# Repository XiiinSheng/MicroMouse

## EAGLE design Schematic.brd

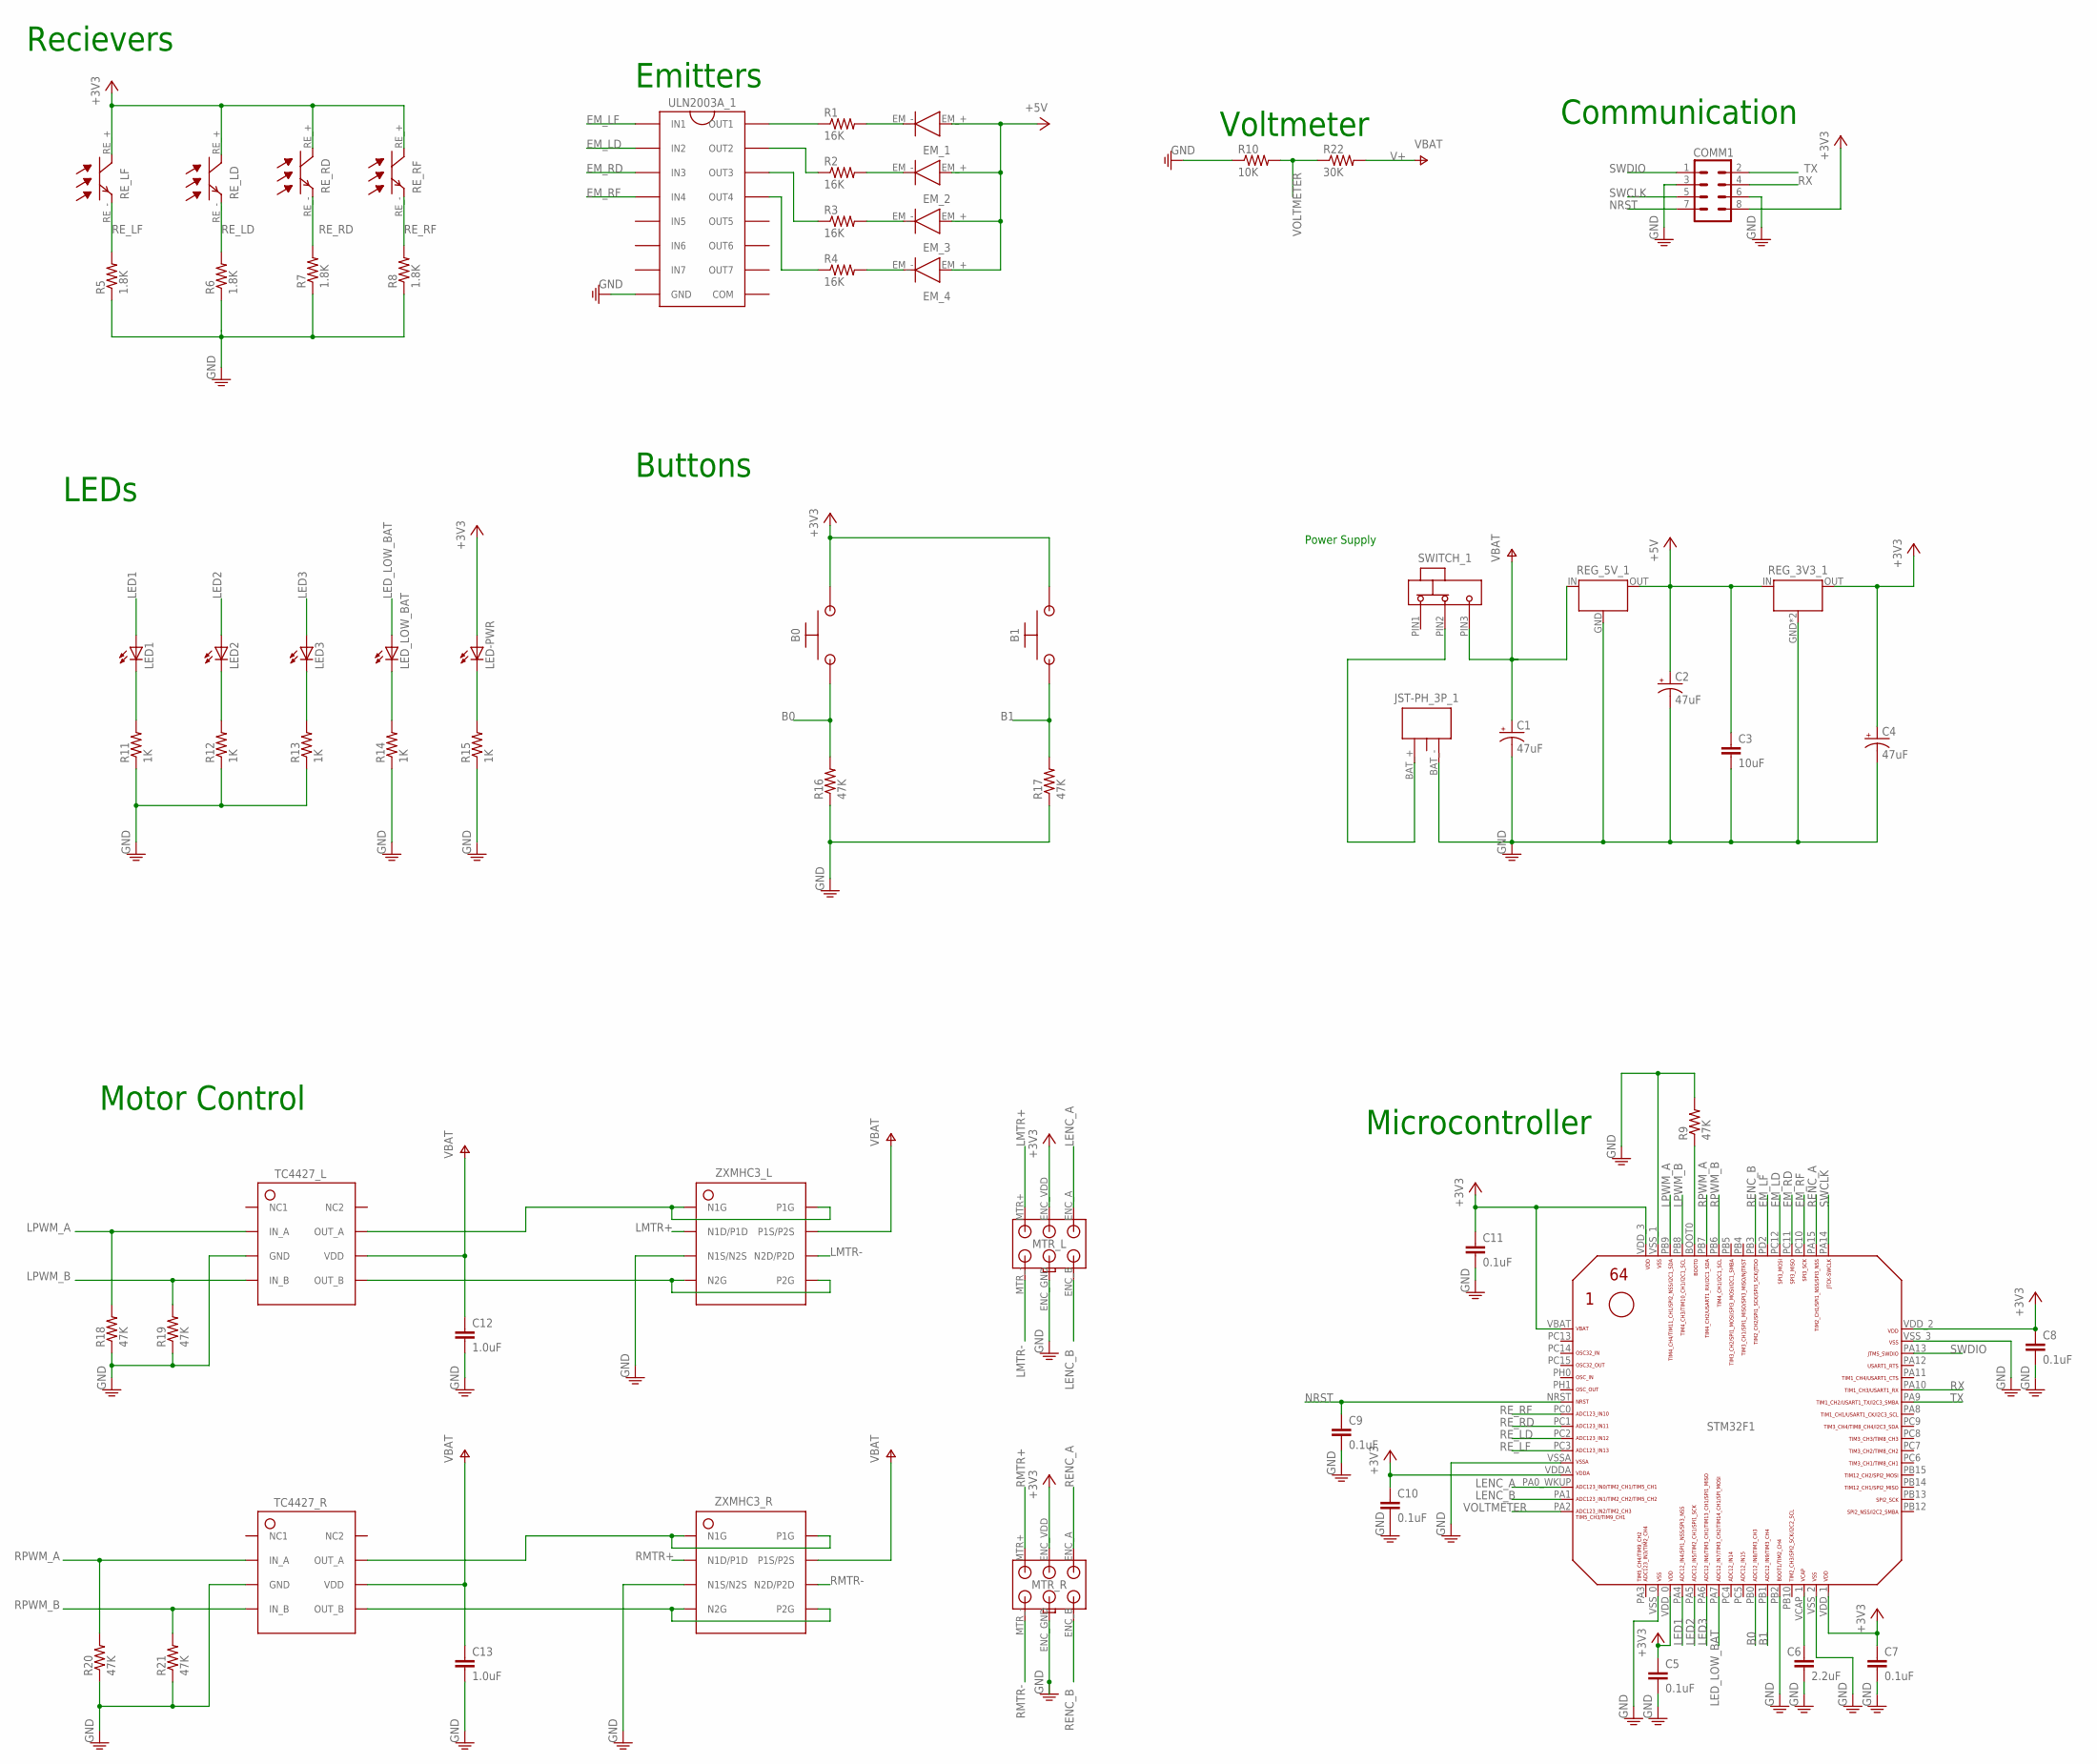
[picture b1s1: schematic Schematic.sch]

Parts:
B0, B1: POLOLU_BUTTON
C1, C2, C4: 47uF; CAP_TANT_1210IN_3528MM
C3: 10uF; 0805
C5, C7, C8, C9, C10, C11: 0.1uF; 0805
C6: 2.2uF; 0805
C12, C13: 1.0uF; 0805
COMM1: M04X2; 2X4
EM_1, EM_2, EM_3, EM_4: SFH4545; EMITTER
JST-PH_3P_1: 3PIN; B3B-PH-K-S
LED1, LED2, LED3: LED; LED-0805
LED-PWR: LED; LED-0805
LED_LOW_BAT: LED; LED-0805
MTR_L: MOTOR_ENCODER_HEADER
MTR_R: MOTOR_ENCODER_HEADER
R1, R2, R3, R4: 16K; 0805
R5, R6, R7, R8: 1.8K; 0805
R9, R16, R17, R18, R19, R20, R21: 47K; 0805
R10: 10K; 0805
R11, R12, R13, R14, R15: 1K; 0805
R22: 30K; 0805
REG_3V3_1: 3V3_REG; SOT223
REG_5V_1: REG_5V_MURATA; 5V_REG_MURATA
RE_LD: TEFT4300; RECEIVER
RE_LF: TEFT4300; RECEIVER
RE_RD: TEFT4300; RECEIVER
RE_RF: TEFT4300; RECEIVER
STM32F1: STM32F4_401_410_411_412_413_446; LQFP64
SWITCH_1: POLOLU_SWITCH
TC4427_L, TC4427_R: TC4427_SOIC8
ULN2003A_1: ULN2003A
ZXMHC3_L, ZXMHC3_R: ZXMHC3

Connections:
+3V3: B0.P$2 (2), B1.P$2 (2), C4.A (+), C5.1, C7.1, C8.1, C10.1, C11.1, COMM1.8, LED-PWR.A, MTR_L.ENC_VDD, MTR_R.ENC_VDD, REG_3V3_1.OUT, RE_LD.RE_+ (C), RE_LF.RE_+ (C), RE_RD.RE_+ (C), RE_RF.RE_+ (C), STM32F1.VBAT, STM32F1.VDDA, STM32F1.VDD_0, STM32F1.VDD_1, STM32F1.VDD_2, STM32F1.VDD_3
+5V: C2.A (+), C3.1, EM_1.EM_+ (+), EM_2.EM_+ (+), EM_3.EM_+ (+), EM_4.EM_+ (+), REG_3V3_1.IN, REG_5V_1.OUT
B0: B0.P$1 (1), R16.2, STM32F1.PB0
B1: B1.P$1 (1), R17.2, STM32F1.PB1
EM_LD: STM32F1.PC12, ULN2003A_1.2B (IN2)
EM_LF: STM32F1.PD2, ULN2003A_1.1B (IN1)
EM_RD: STM32F1.PC11, ULN2003A_1.3B (IN3)
EM_RF: STM32F1.PC10, ULN2003A_1.4B (IN4)
GND: C1.C (-), C2.C (-), C3.2, C4.C (-), C5.2, C6.2, C7.2, C8.2, C9.2, C10.2, C11.2, C12.2, C13.2, COMM1.3, COMM1.6, JST-PH_3P_1.BAT_-, MTR_L.ENC_GND, MTR_R.ENC_GND, R5.1, R6.1, R7.1, R8.1, R9.2, R10.1, R11.1, R12.1, R13.1, R14.1, R15.1, R16.1, R17.1, R18.1, R19.1, R20.1, R21.1, REG_3V3_1.GND, REG_3V3_1.GND2 (GND), REG_5V_1.GND, STM32F1.PB2, STM32F1.VSSA, STM32F1.VSS_0, STM32F1.VSS_1, STM32F1.VSS_2 (VCAP_1), STM32F1.VSS_3 (VCAP_2), TC4427_L.GND, TC4427_R.GND, ULN2003A_1.GND, ZXMHC3_L.N1S/N2S, ZXMHC3_R.N1S/N2S
LED1: LED1.A, STM32F1.PA4
LED2: LED2.A, STM32F1.PA5
LED3: LED3.A, STM32F1.PA6
LED_LOW_BAT: LED_LOW_BAT.A, STM32F1.PA7
LENC_A: MTR_L.ENC_A, STM32F1.PA0_WKUP (PA0_AKUP)
LENC_B: MTR_L.ENC_B, STM32F1.PA1
LMTR+: MTR_L.MTR+ (MTR_+), ZXMHC3_L.N1D/P1D
LMTR-: MTR_L.MTR_-, ZXMHC3_L.N2D/P2D
LPWM_A: R18.2, STM32F1.PB9, TC4427_L.IN_A
LPWM_B: R19.2, STM32F1.PB8, TC4427_L.IN_B
unnamed: R1.1, ULN2003A_1.1C (OUT1)
unnamed: R2.1, ULN2003A_1.2C (OUT2)
unnamed: R3.1, ULN2003A_1.3C (OUT3)
unnamed: R4.1, ULN2003A_1.4C (OUT4)
unnamed: EM_1.EM_- (-), R1.2
unnamed: EM_2.EM_- (-), R2.2
unnamed: EM_3.EM_- (-), R3.2
unnamed: EM_4.EM_- (-), R4.2
unnamed: JST-PH_3P_1.BAT_+, SWITCH_1.PIN2
unnamed: R9.1, STM32F1.BOOT0
unnamed: C6.1, STM32F1.VCAP_1 (PB11)
unnamed: TC4427_L.OUT_B, ZXMHC3_L.N2G, ZXMHC3_L.P2G
unnamed: TC4427_L.OUT_A, ZXMHC3_L.N1G, ZXMHC3_L.P1G
unnamed: TC4427_R.OUT_A, ZXMHC3_R.N1G, ZXMHC3_R.P1G
unnamed: TC4427_R.OUT_B, ZXMHC3_R.N2G, ZXMHC3_R.P2G
unnamed: LED1.C, R11.2
unnamed: LED2.C, R12.2
unnamed: LED3.C, R13.2
unnamed: LED_LOW_BAT.C, R14.2
unnamed: LED-PWR.C, R15.2
NRST: C9.1, COMM1.7, STM32F1.NRST
RENC_A: MTR_R.ENC_A, STM32F1.PA15
RENC_B: MTR_R.ENC_B, STM32F1.PB3
RE_LD: R6.2, RE_LD.RE_- (E), STM32F1.PC2
RE_LF: R5.2, RE_LF.RE_- (E), STM32F1.PC3
RE_RD: R7.2, RE_RD.RE_- (E), STM32F1.PC1
RE_RF: R8.2, RE_RF.RE_- (E), STM32F1.PC0
RMTR+: MTR_R.MTR+ (MTR_+), ZXMHC3_R.N1D/P1D
RMTR-: MTR_R.MTR_-, ZXMHC3_R.N2D/P2D
RPWM_A: R20.2, STM32F1.PB7, TC4427_R.IN_A
RPWM_B: R21.2, STM32F1.PB6, TC4427_R.IN_B
RX: COMM1.4, STM32F1.PA10
SWCLK: COMM1.5, STM32F1.PA14
SWDIO: COMM1.1, STM32F1.PA13
TX: COMM1.2, STM32F1.PA9
V+: C1.A (+), C12.1, C13.1, R22.2, REG_5V_1.IN, SWITCH_1.PIN3, TC4427_L.VDD, TC4427_R.VDD, ZXMHC3_L.P1S/P2S, ZXMHC3_R.P1S/P2S
VOLTMETER: R10.2, R22.1, STM32F1.PA2

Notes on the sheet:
Emitters
Power Supply
Communication
Recievers
Microcontroller
Motor Control
LEDs
Buttons
Voltmeter

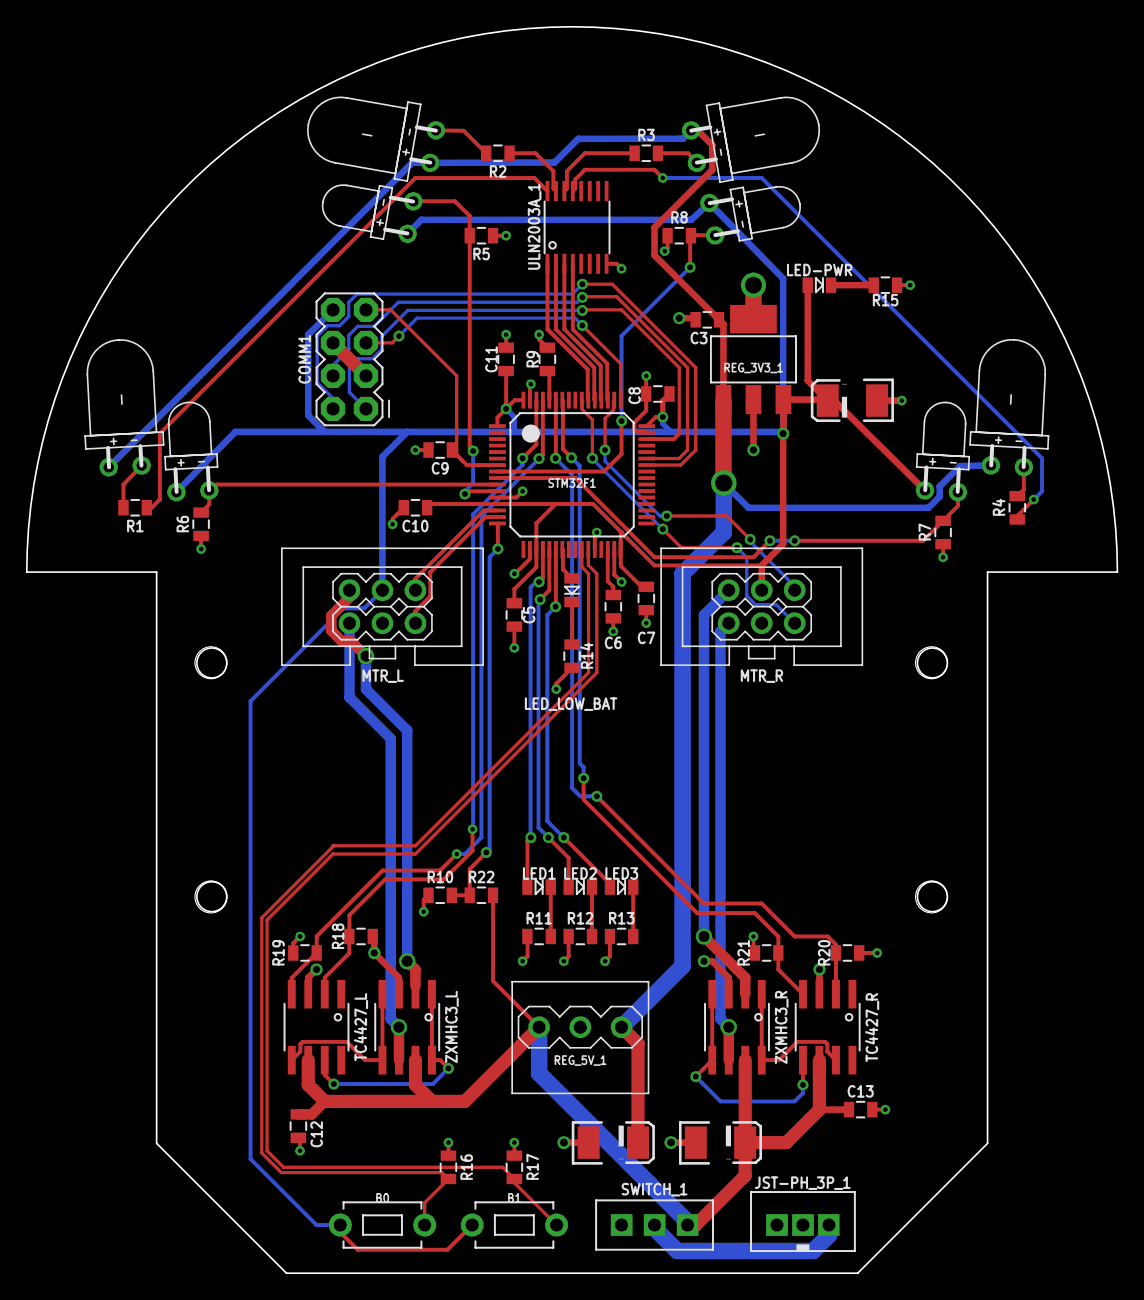
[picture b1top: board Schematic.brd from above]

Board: 2 copper layers, 84.0 x 96.0 mm, 64 parts (0 on the bottom side), 56 nets.

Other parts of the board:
U$2: MOUSE_OUTLINE_2WHEEL

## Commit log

2020-01-25 error fix
2020-01-25 Created PCB
2020-01-26 Placed components on PCB
2020-01-26 Autoroute only
2020-01-26 added gitignore
2020-01-26 gitignore
2020-01-26 update gitignore
2020-02-01 013120meeting
2020-02-03 test
2020-02-04 handroute
2020-02-05 Routing
2020-02-05 Finished routing
2020-02-07 changes trace width
2020-02-19 Organize files
2020-03-02 Corrected GND plane connections
2020-03-02 Minor fix
2020-03-02 Fix errors
2020-03-02 03022020 meeting
2020-03-04 slikscreen edit
2020-03-08 generated gerber files
2020-03-08 clean up
